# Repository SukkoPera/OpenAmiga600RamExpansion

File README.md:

# OpenAmiga600RamExpansion
OpenAmiga600RamExpansion is an Open Hardware 1 MB Chip RAM Expansion for the Commodore Amiga 600 Computer with optional Real Time Clock.

### Summary
The Amiga 600 computer by Commodore originally came with 1 MB of Chip RAM. Like all "compact" Amiga models, it has a trapdoor in the bottom, through which a memory expansion can be installed, bringing the chip RAM to a maximum of 2 MB.

Back in the day, some expansions also came with a Real-Time Clock (RTC), which allowed the Amiga to keep track of the current date and time, which is most useful if you use AmigaDOS a lot. While this was mostly ordinary for Amiga 500 expansions, it was not so common on those for the Amiga 600, and even most expansions designed today do not bear an RTC circuit.

OpenAmiga600RamExpansion is an Open Hardware implementation of such an expansion, including the RTC.

Once you have maximized the Chip RAM in your A600, you might be interested in adding some **Fast** RAM as well: please check out [OpenAmiga600FastRamExpansion](https://github.com/SukkoPera/OpenAmiga600FastRamExpansion) in case.

### Components
#### Connector
The female connector for the male edge connector on the A600 PCB is probably the hardest part to get hold of. Many people use PCI connectors, which have the correct pitch but are longer and need to be trimmed. They are also hard to solder, most of the time. This project uses [a connector](https://coolcomponents.co.uk/products/edge-connector-for-bbc-micro-bit) that is normally used with the [micro:bit educational computer](http://microbit.org) instead. It was discovered by chance to be a perfect fit for the the A600, cheap and reliable.

#### Memory
The required RAM Type is 4 Mbit (256k×16) DRAM in the SOJ-40 package with up to 70-80 ns access time, e.g.:

|Model         |Maker           |Tested                                                                              |Working                                                                               |Data Sheet                                                                                                                                                                 |Notes                                                                                |
|--------------|----------------|:----------------------------------------------------------------------------------:|:------------------------------------------------------------------------------------:|:-------------------------------------------------------------------------------------------------------------------------------------------------------------------------:|-------------------------------------------------------------------------------------|
|AS4C256K16E0  |Alliance|  | |          | Tested by [Marcovecchio](https://github.com/Marcovecchio). Used `-50JC` speed variant.  | |                               |                                                                                     |
|HM514260AJ8   |Hitachi         |  |                                                                                      |                                                                                                                                                                           |                                                                                     |
|HM514260JP8   |Hitachi         |  |                                                                                      |                                                                                                                                                                           |                                                                                     |
|HY514260BJC   |Hyundai |  | |          | Tested by [Marcovecchio](https://github.com/Marcovecchio). Used `-70` speed variant.  | 
|KM416C256BJ   |Samsung |  | |          | Tested by [tehKaiN](https://github.com/tehKaiN). Used `-4` speed variant. |
|M514260C      |OKI     |  | |          | Tested by [tehKaiN](https://github.com/tehKaiN). Used `-60J` speed variant. |
|IC41C16257-35K|ICSI            ||  |      |Tested by go0se@AmiBay. _-S_ version should work, too. Do NOT use _LV_ versions.              |
|T224162B      |Tmtech  |  | |          | Tested by [Occupied](https://github.com/Occupied) Used `-35J` speed variant. |              |
|µPD424260     |NEC             |  |                                                                                      |                                                                                                                                                                           |                                                                                     |
|V53C16256HK50 |MOSEL VITELIC   ||  |       |                                                                                     |
|V53C16258HK30/35/50 |MOSEL VITELIC   ||  |       |                                                                                     |
|V53C16258SHK50|MOSEL VITELIC   ||  |      |                                                                                     |

Most of these chips can be found on eBay or on AliExpress very cheaply (i.e.: 1-2€ each).

Normally it is not necessary to mount all the decoupling capacitors. I usually skip C2 and C4. All of them are 100nF in the 0805 package anyway. An additional 10uF electrolytic capacitor can be mounted at C9, if needed. Might be a good idea if using a *Vampire* board or a power-hungry machine.

RAM chips can either be soldered directly on the board or installed in sockets. While soldering the chips might not be trivial for the unexperienced, sockets for the SOJ-40 package are quite expensive and not really easier to solder either, so the choice is up to you.

#### RTC
The entire RTC circuit is optional. It has been designed for an Epson [RTC62421](http://pdf.datasheetcatalog.com/datasheets/90/339927_DS.pdf) or [RTC72421](http://pdf.datasheetcatalog.com/datasheet/epson/RTC-72423.pdf), which don't need an external crystal nor any calibration. Both can be bought very cheaply from China: they will most likely be second-hand "pulls", but usually they will work fine.

The other components have some degree of flexibility:
- C7: 100 nF 0805 capacitor
- C8: >= 2.2 μF >= 10 V 1206 tantalum capacitor
- R1, R2, R3: 10K 0805 resistor
- R4, R5: 220-470 0805 resistor
- D1: BAT721C or BAT54C diode
- Battery Holder: Some cheap eBay one, usually called *BS-7*
- Battery: CR2032 3V Non-Rechargeable Lithium (a new one will last years)

Note that if you plan to shelve your Amiga or not to use it for a while, **you are recommended to remove the RTC battery**. Failing to do so killed many A500+ computers and many A501 expansions in the past. The CR2032 battery used in this project is probably safer than the barrel batteries used in those devices, but still I would not leave one in an unused Amiga. You have been warned.

### Installation
After everything has been soldered, just open the trapdoor on your Amiga, install the expansion (the correct orientation is with the chips closer to the keyboard) and put the cover back on.

I recommend to run [Amiga Test Kit (formerly SysTest)](https://github.com/keirf/Amiga-Stuff) then. Use the Memory option (<kbd>F1</kbd>), it must show 2 MB of Chip RAM. Then start the Memory Test (<kbd>F1</kbd> again) and let it run for 50-100 rounds: if it doesn't find any errors, you are probably good to go.

Amiga Test Kit also has an option for reading and resetting the RTC (<kbd>F7</kbd> then <kbd>F3</kbd>), so try that as well. If you are using Amiga Test Kit or SysTest >= 1.2 you can also set the date and time with it, otherwise you will have to use other tools (Workbench is a good candidate).

### Issues
The board has been thoroughly tested and it works perfectly, but if you are trying to understand how it works, please be aware that [there are some oddities in the schematics](https://github.com/SukkoPera/OpenAmiga600RamExpansion/issues/7).

### License
The OpenAmiga600RamExpansion documentation, including the design itself, is copyright &copy; SukkoPera 2019.

OpenAmiga600RamExpansion is Open Hardware licensed under the [CERN OHL v. 1.2](http://ohwr.org/cernohl).

You may redistribute and modify this documentation under the terms of the CERN OHL v.1.2. This documentation is distributed *as is* and WITHOUT ANY EXPRESS OR IMPLIED WARRANTIES whatsoever with respect to its functionality, operability or use, including, without limitation, any implied warranties OF MERCHANTABILITY, SATISFACTORY QUALITY, FITNESS FOR A PARTICULAR PURPOSE or infringement. We expressly disclaim any liability whatsoever for any direct, indirect, consequential, incidental or special damages, including, without limitation, lost revenues, lost profits, losses resulting from business interruption or loss of data, regardless of the form of action or legal theory under which the liability may be asserted, even if advised of the possibility or likelihood of such damages.

A copy of the full license is included in file [LICENSE.pdf](LICENSE.pdf), please refer to it for applicable conditions. In order to properly deal with its terms, please see file [LICENSE_HOWTO.pdf](LICENSE_HOWTO.pdf).

The contact points for information about manufactured Products (see section 4.2) are listed in file [PRODUCT.md](PRODUCT.md).

Any modifications made by Licensees (see section 3.4.b) shall be recorded in file [CHANGES.md](CHANGES.md).

The Documentation Location of the original project is https://github.com/SukkoPera/OpenAmiga600RamExpansion/.

### Support the Project
Since the project is open you are free to get the PCBs made by your preferred manufacturer, however in case you want to support the development, you can order them from PCBWay through this link:

You get my gratitude and cheap, professionally-made and good quality PCBs, I get some credit that will help with this and [other projects](https://www.pcbway.com/project/member/shareproject/?bmbid=41100). You won't even have to worry about the various PCB options, it's all pre-configured for you!

Also, if you still have to register to that site, [you can use this link](https://www.pcbway.com/setinvite.aspx?inviteid=41100) to get some bonus initial credit (and yield me some more).

Again, if you want to use another manufacturer, feel free to, don't feel obligated :). But then, you can buy me a coffee if you want:

### Thanks
- Thanks to the guys at the Italian Amiga Page forum, in particular:
  - fpmpaolo for suggesting the idea of making such a board
  - cpiace64 for providing me with a board to use as a template
  - majinga for helping with the testing
- The RTC circuit was copied shamelessly from the [Amiga 500 Expansion designed by PeteAU](http://eab.abime.net/showthread.php?t=85395) (which in turn probably copied it from Commodore).
- Footprint for [micro:bit edge connector](https://coolcomponents.co.uk/products/edge-connector-for-bbc-micro-bit) derived from work by [Anthony Kirby](https://github.com/anthonykirby/kicad_microbit_connector).
- Footprint for BS-7 Battery Holder taken from the [digikey-kicad-library](https://github.com/digikey/digikey-kicad-library).

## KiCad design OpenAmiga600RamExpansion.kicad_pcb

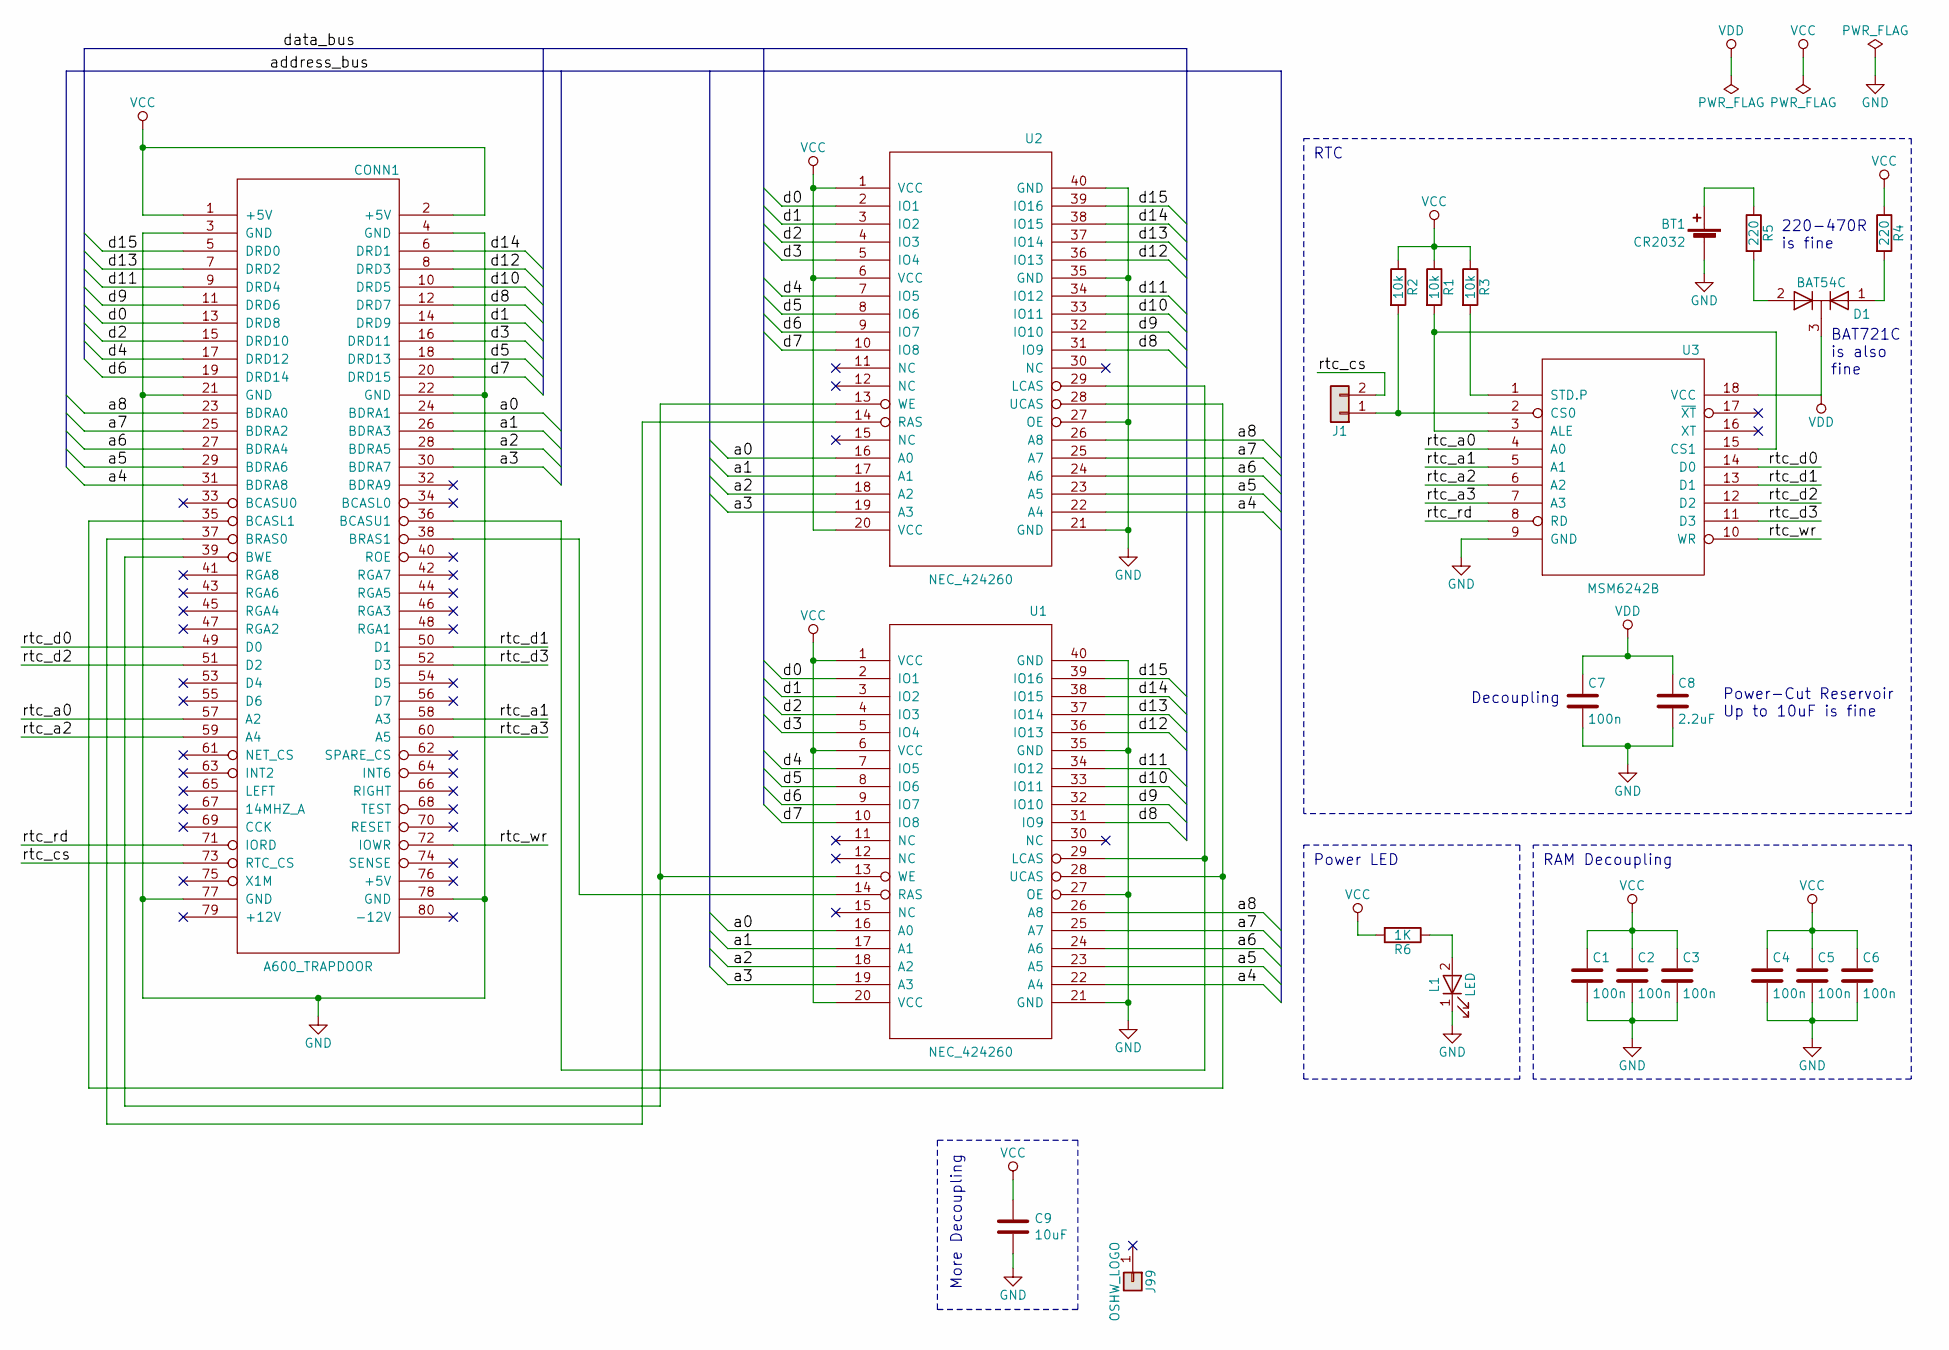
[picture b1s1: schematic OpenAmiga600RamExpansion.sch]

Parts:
BT1: CR2032; Battery_Holder_Coin_2032_BS-7
C1, C2, C3, C4, C5, C6, C7: 100n; C_0805_HandSoldering
C8: 2.2uF; C_1206_HandSoldering
C9: 10uF; CP_Radial_D5.0mm_P2.00mm
CONN1: A600_TRAPDOOR; 4UCON_10156_90deg
D1: BAT54C; SOT-23_Handsoldering
J1: Conn_01x02; Pin_Header_Straight_1x02-ModSilkS
J99: OSHW_LOGO; Logo_copper_OSHW_6x6mm
L1: LED; LED_0805_HandSoldering_ModSilkS
R1, R2, R3: 10k; R_0805_HandSoldering
R4, R5: 220; R_0805_HandSoldering
R6: 1K; R_0805_HandSoldering
U1, U2: NEC_424260; SOJ-40-Socket-LongPads
U3: MSM6242B; DIP-18_W7.62mm_Socket

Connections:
/a0: CONN1.24 (BDRA1), U1.16 (A0), U2.16 (A0)
/a1: CONN1.26 (BDRA3), U1.17 (A1), U2.17 (A1)
/a2: CONN1.28 (BDRA5), U1.18 (A2), U2.18 (A2)
/a3: CONN1.30 (BDRA7), U1.19 (A3), U2.19 (A3)
/a4: CONN1.31 (BDRA8), U1.22 (A4), U2.22 (A4)
/a5: CONN1.29 (BDRA6), U1.23 (A5), U2.23 (A5)
/a6: CONN1.27 (BDRA4), U1.24 (A6), U2.24 (A6)
/a7: CONN1.25 (BDRA2), U1.25 (A7), U2.25 (A7)
/a8: CONN1.23 (BDRA0), U1.26 (A8), U2.26 (A8)
/d0: CONN1.13 (DRD8), U1.2 (IO1), U2.2 (IO1)
/d1: CONN1.14 (DRD9), U1.3 (IO2), U2.3 (IO2)
/d2: CONN1.15 (DRD10), U1.4 (IO3), U2.4 (IO3)
/d3: CONN1.16 (DRD11), U1.5 (IO4), U2.5 (IO4)
/d4: CONN1.17 (DRD12), U1.7 (IO5), U2.7 (IO5)
/d5: CONN1.18 (DRD13), U1.8 (IO6), U2.8 (IO6)
/d6: CONN1.19 (DRD14), U1.9 (IO7), U2.9 (IO7)
/d7: CONN1.20 (DRD15), U1.10 (IO8), U2.10 (IO8)
/d8: CONN1.12 (DRD7), U1.31 (IO9), U2.31 (IO9)
/d9: CONN1.11 (DRD6), U1.32 (IO10), U2.32 (IO10)
/d10: CONN1.10 (DRD5), U1.33 (IO11), U2.33 (IO11)
/d11: CONN1.9 (DRD4), U1.34 (IO12), U2.34 (IO12)
/d12: CONN1.8 (DRD3), U1.36 (IO13), U2.36 (IO13)
/d13: CONN1.7 (DRD2), U1.37 (IO14), U2.37 (IO14)
/d14: CONN1.6 (DRD1), U1.38 (IO15), U2.38 (IO15)
/d15: CONN1.5 (DRD0), U1.39 (IO16), U2.39 (IO16)
/rtc_a0: CONN1.57 (A2), U3.4 (A0)
/rtc_a1: CONN1.58 (A3), U3.5 (A1)
/rtc_a2: CONN1.59 (A4), U3.6 (A2)
/rtc_a3: CONN1.60 (A5), U3.7 (A3)
/rtc_cs: CONN1.73 (RTC_CS), J1.2
/rtc_d0: CONN1.49 (D0), U3.14 (D0)
/rtc_d1: CONN1.50 (D1), U3.13 (D1)
/rtc_d2: CONN1.51 (D2), U3.12 (D2)
/rtc_d3: CONN1.52 (D3), U3.11 (D3)
/rtc_rd: CONN1.71 (IORD), U3.8 (RD)
/rtc_wr: CONN1.72 (IOWR), U3.10 (WR)
GND: BT1.2 (-), C1.2, C2.2, C3.2, C4.2, C5.2, C6.2, C7.2, C8.2, C9.2, CONN1.3 (GND), CONN1.4 (GND), CONN1.21 (GND), CONN1.22 (GND), CONN1.77 (GND), CONN1.78 (GND), L1.1 (K), U1.21 (GND), U1.27 (OE), U1.35 (GND), U1.40 (GND), U2.21 (GND), U2.27 (OE), U2.35 (GND), U2.40 (GND), U3.9 (GND)
unnamed: BT1.1 (+), R5.1
unnamed: CONN1.35 (BCASL1), U1.28 (UCAS), U2.28 (UCAS)
unnamed: CONN1.36 (BCASU1), U1.29 (LCAS), U2.29 (LCAS)
unnamed: CONN1.37 (BRAS0), U2.14 (RAS)
unnamed: CONN1.38 (BRAS1), U1.14 (RAS)
unnamed: CONN1.39 (BWE), U1.13 (WE), U2.13 (WE)
unnamed: D1.1 (A), R4.2
unnamed: D1.2 (A), R5.2
unnamed: J1.1, R2.2, U3.2 (CS0)
unnamed: L1.2 (A), R6.1
unnamed: R1.2, U3.3 (ALE), U3.15 (CS1)
unnamed: R3.2, U3.1 (STD.P)
VCC: C1.1, C2.1, C3.1, C4.1, C5.1, C6.1, C9.1, CONN1.1 (+5V), CONN1.2 (+5V), R1.1, R2.1, R3.1, R4.1, R6.2, U1.1 (VCC), U1.6 (VCC), U1.20 (VCC), U2.1 (VCC), U2.6 (VCC), U2.20 (VCC)
VDD: C7.1, C8.1, D1.3 (K), U3.18 (VCC)

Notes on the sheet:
RTC
Decoupling
RAM Decoupling
Power-Cut Reservoir Up to 10uF is fine
220-470R is fine
BAT721C is also fine
Power LED
More Decoupling

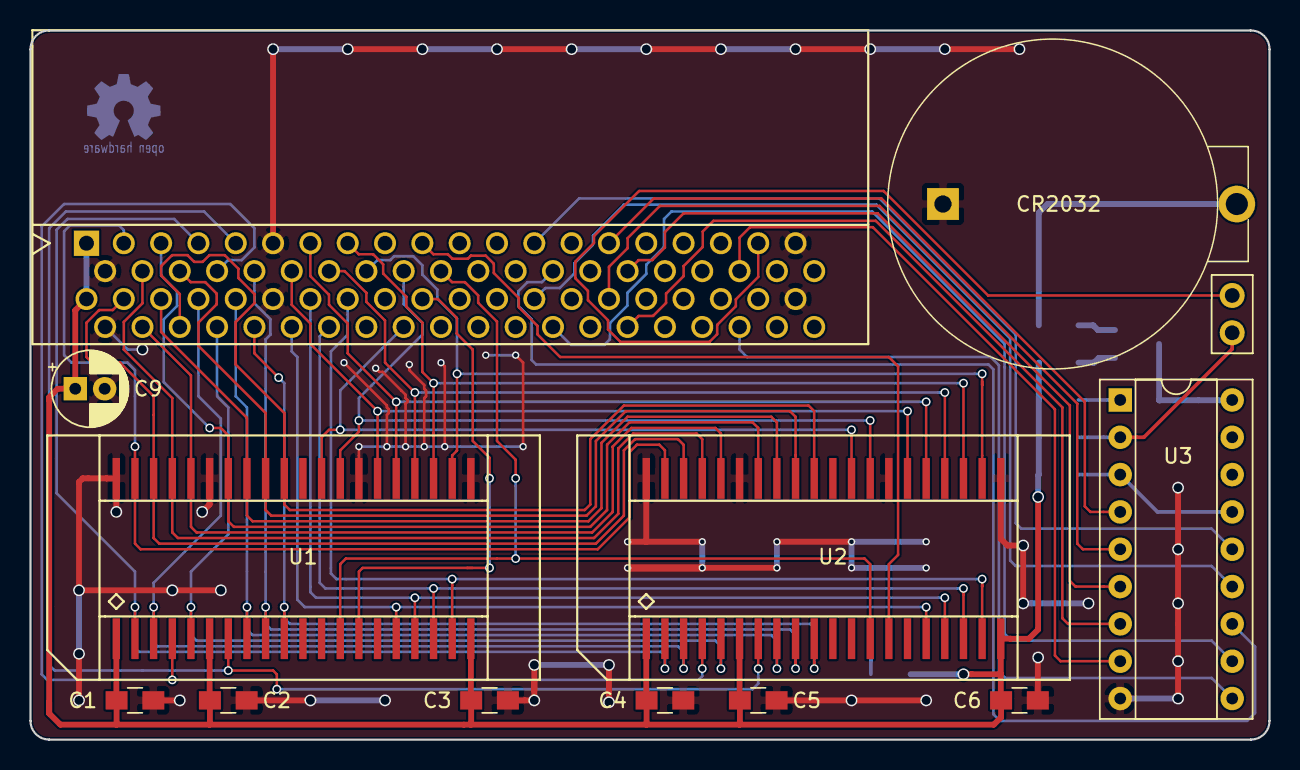
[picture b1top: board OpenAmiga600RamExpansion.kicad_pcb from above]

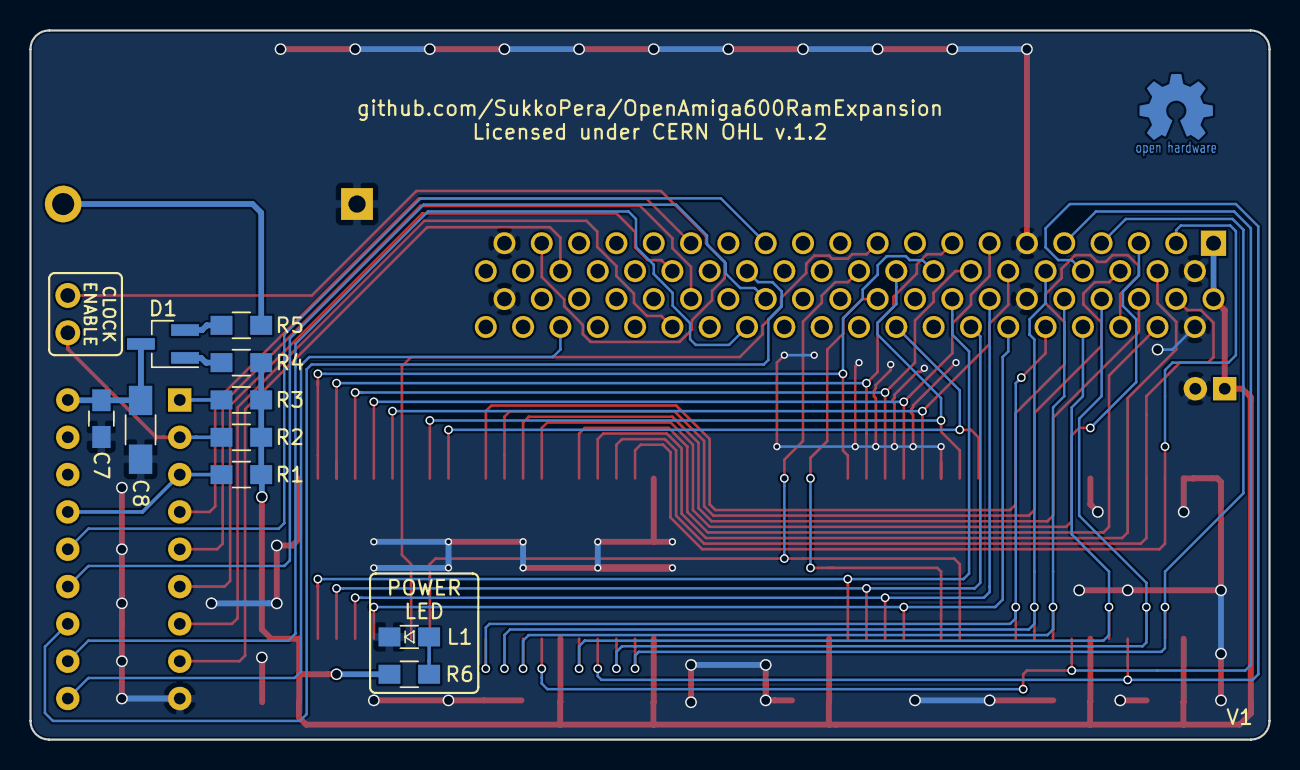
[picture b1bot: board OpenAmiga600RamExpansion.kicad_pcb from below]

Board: 2 copper layers, 84.3 x 48.3 mm, 24 parts (11 on the bottom side), 51 nets.

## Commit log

2018-06-21 Schematics should be final. PCB will come, one day...
2018-06-21 Add some info
2018-06-21 Make RAM chip pads longer
2018-06-24 Fix error in RTC power circuit
2018-06-26 Reposition some RTC components
2018-06-26 Minor silkscreen fixes
2018-06-28 The sweetest perfection ;)
2018-07-27 Add images
2018-07-27 Use smaller image
2018-07-27 Go even smaller!
2018-07-27 16px
2018-09-10 Add RAM compatibility list and RTC BOM
2018-09-10 Use HandSoldering version of SOT-23 footprint
2018-09-10 Switch to KiCad 5
2018-09-10 Add (optional) decoupling electrolytic cap, just in case
2018-09-10 Add renders
2018-09-10 Update schematic
2018-11-05 Minor corrections
2019-04-16 Update README.md
    Fix #2.
2019-05-08 Samsung KM416C256BJ and OKI M514260C compatibility
    I'm kinda nuts so I've soldered my expansion two different chips and they work! Tested under Advanced Amiga Analyzer's memtest 3 times.
2019-05-16 Add license
2019-05-16 SysTest -> Amiga Test Kit
2019-05-16 Add license on schematics PDF
2021-07-09 Update README.md
    Adding more RAM models to compatibility list
2021-07-17 Add Tmtech T224162B-35J to compatibility list
    Tested with several passes in Amiga Test Kit without problems
2026-02-13 Update README to remove outdated content
    Removed old Ko-fi button and help section from README.

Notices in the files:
OpenAmiga600RamExpansion.kicad_pcb:
Licensed under CERN OHL v.1.2
